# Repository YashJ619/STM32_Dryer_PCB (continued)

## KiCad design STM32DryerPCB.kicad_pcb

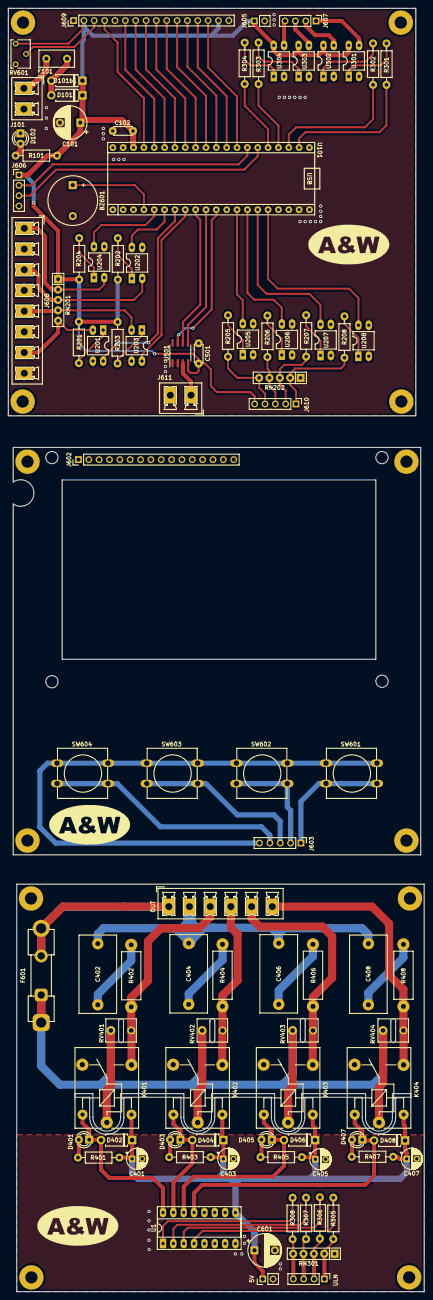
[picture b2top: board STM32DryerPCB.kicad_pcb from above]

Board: 2 copper layers, 102.1 x 315.0 mm, 111 parts (0 on the bottom side), 82 nets.

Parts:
BZ601: Buzzer; Buzzer_12x9.5RM7.6
C101: 220uF16v; CP_Radial_D8.0mm_P5.00mm
C102: 100nF; C_Disc_D4.3mm_W1.9mm_P5.00mm
C401, C403, C405, C407: 22uF; CP_Radial_D5.0mm_P2.50mm
C402, C404, C406, C408: 0.1uF; C_Rect_L19.0mm_W9.0mm_P15.00mm_MKS4
C501: 100n; C_Disc_D4.3mm_W1.9mm_P5.00mm
C601: 220uF16V; CP_Radial_D8.0mm_P5.00mm
D101, D101b1: 1N5819; D_A-405_P7.62mm_Horizontal
D102, D401, D403, D405, D407: LED; LED_D3.0mm
D402, D404, D406, D408: 1N4148; D_A-405_P7.62mm_Horizontal
F101: 1A; Fuse_Littelfuse_395Series
F601: 5A; Fuseholder_Clip-5x20mm_Keystone_3518P_Inline_P23.11x6.76mm_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
H601, H601#2, H601#4, H601#5: MountingHole; MountingHole_3mm
H601#3, H602, H603, H604, H605, H606, H607, H608, H609, H610, H611, H612: MountingHole; MountingHole_3mm_Pad
J101: DC_Con; PhoenixContact_MCV_1,5_2-G-5.08_1x02_P5.08mm_Vertical
J602: B1_B2_LCD; PinHeader_1x16_P2.54mm_Vertical
J603: B1_B2_KEYPAD; PinHeader_1x05_P2.54mm_Vertical
J605: B2_B3_PW; PinHeader_1x02_P2.54mm_Vertical
J606: B2_UART; PinHeader_1x04_P2.54mm_Vertical
J607: B2_B3_ULN; PinHeader_1x04_P2.54mm_Vertical
J608: B2_INPUT; PhoenixContact_MCV_1,5_8-G-5.08_1x08_P5.08mm_Vertical
J609: B2_B1_LCD; PinHeader_1x16_P2.54mm_Vertical
J610: B2_B1_KEYPAD; PinHeader_1x05_P2.54mm_Vertical
J611: B2_TEMP; PhoenixContact_MCV_1,5_2-G-5.08_1x02_P5.08mm_Vertical
J612: B3_B2_PW; PinHeader_1x02_P2.54mm_Vertical
J613: B3_output; PhoenixContact_MCV_1,5_6-G-5.08_1x06_P5.08mm_Vertical
J614: B3_B2_ULN; PinHeader_1x04_P2.54mm_Vertical
K401, K402, K403, K404: DC_5V; Relay_SPDT_SANYOU_SRD_Series_Form_C
R101: 1k; R_Axial_DIN0207_L6.3mm_D2.5mm_P10.16mm_Horizontal
R201, R202, R203, R204, R205, R206, R207, R208, R301, R302, R303, R304: 470R; R_Axial_DIN0207_L6.3mm_D2.5mm_P10.16mm_Horizontal
R305, R306, R307, R308, R401, R403, R405, R407: 1K; R_Axial_DIN0207_L6.3mm_D2.5mm_P10.16mm_Horizontal
R402, R404, R406, R408: 100R; R_Axial_DIN0414_L11.9mm_D4.5mm_P15.24mm_Horizontal
RN201, RN202, RN301: 10K; R_Array_SIP5
RV401, RV402, RV403, RV404: 10D431K; RV_Disc_D7mm_W5.7mm_P5mm
RV601: 10K; Potentiometer_Bourns_3266W_Vertical
SW601, SW602, SW603, SW604: SW_Push; SW_PUSH-12mm
U1: ULN2003A; DIP-16_W7.62mm_Socket_LongPads
U101: BluePill
U201, U202, U203, U204, U205, U206, U207, U208, U301, U302, U303, U304: PC817; DIP-4_W7.62mm_LongPads
U501: MAX6675; SOIC-8_3.9x4.9mm_P1.27mm

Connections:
#DRUM_LEFT: D407.1 (K), D408.2 (A), K404.5, U1.13 (O4)
#DRUM_RIGHT: D405.1 (K), D406.2 (A), K403.5, U1.14 (O3)
#FAN: D401.1 (K), D402.2 (A), K401.5, U1.16 (O1)
#HEATER: D403.1 (K), D404.2 (A), K402.5, U1.15 (O2)
+5V: C101.1, C102.1, C401.1, C403.1, C405.1, C407.1, C501.2, C601.1, D101.1 (K), D101b1.1 (K), D402.1 (K), D404.1 (K), D406.1 (K), D408.1 (K), J602.2, J602.15, J603.5, J605.1, J606.1, J609.2, J609.15, J610.5, J612.1, K401.2, K402.2, K403.2, K404.2, R101.2, R201.1, R202.1, R203.1, R204.1, R401.1, R403.1, R405.1, R407.1, RN201.1 (common), RV601.1, SW601.1, SW602.1, SW603.1, SW604.1, U1.9 (COM), U101.38 (5V), U301.4, U302.4, U303.4, U304.4, U501.4 (VCC)
/CONNECTORS/VO: J602.3, J609.3, RV601.2
/ULN2003/->FAN: R308.2, U1.1 (I1)
/ULN2003/->HEATER: R307.2, U1.2 (I2)
/ULN2003/->LEFT: R305.2, U1.4 (I4)
/ULN2003/->RIGHT: R306.2, U1.3 (I3)
BUZZER: BZ601.1 (-), U101.4 (PC15)
CS1: U101.9 (PA4), U501.6 (~CS)
DLEFT_ULNIN: J607.1, J614.1, R305.1, RN301.2 (R1), U301.3
DOOR_SW: U101.5 (PA0), U204.4
DOOR_SW_IN: J608.1, RN201.2 (R1), U204.2
DRIGHT_ULNIN: J607.2, J614.2, R306.1, RN301.3 (R2), U302.3
DRUM_LEFT: R301.1, U101.22 (PB13)
DRUM_LEFT_LINE: J613.6, K404.3, R408.1, RV404.2
DRUM_RIGHT: R302.1, U101.23 (PB14)
DRUM_RIGHT_LINE: J613.5, K403.3, R406.1, RV403.2
FAN: R304.1, U101.25 (PA8)
FAN_LINE: J613.3, K401.3, R402.1, RV401.2
FAN_ULNIN: J607.4, J614.4, R308.1, RN301.5 (R4), U304.3
FN_KEY_SW: U101.13 (PB0), U205.4
FN_KEY_SW_IN: J603.4, J610.4, R205.1, RN202.5 (R4), SW604.2
GND: BZ601.2 (+), C101.2, C102.2, C401.2, C403.2, C405.2, C407.2, C501.1, C601.2, D102.1 (K), J101.2, J602.1, J602.5, J602.16, J605.2, J606.4, J608.2, J608.4, J608.6, J608.8, J609.1, J609.5, J609.16, J611.2, J612.2, RN202.1 (common), RN301.1 (common), RV601.3, U1.8 (GND), U101.19 (GND), U101.20 (GND), U101.39 (GND), U201.3, U202.3, U203.3, U204.3, U205.2, U205.3, U206.2, U206.3, U207.2, U207.3, U208.2, U208.3, U301.2, U302.2, U303.2, U304.2, U501.1 (GND), U501.2 (T-)
HEATER: R303.1, U101.24 (PB15)
HEATER_LINE: J613.4, K402.3, R404.1, RV402.2
HEATER_SW: U101.8 (PA3), U203.4
HEATER_SW_IN: J608.5, RN201.4 (R3), U203.2
HEATER_ULNIN: J607.3, J614.3, R307.1, RN301.4 (R3), U303.3
HIGH_KEY_SW: U101.15 (PB10), U207.4
HIGH_KEY_SW_IN: J603.2, J610.2, R207.1, RN202.3 (R2), SW602.2
LCD_D0: J602.7, J609.7, U101.35 (PB7)
LCD_D1: J602.8, J609.8, U101.34 (PB6)
LCD_D2: J602.9, J609.9, U101.33 (PB5)
LCD_D3: J602.10, J609.10, U101.32 (PB4)
LCD_D4: J602.11, J609.11, U101.31 (PB3)
LCD_D5: J602.12, J609.12, U101.30 (PA15)
LCD_D6: J602.13, J609.13, U101.29 (PA12)
LCD_D7: J602.14, J609.14, U101.28 (PA11)
LCD_EN: J602.6, J609.6, U101.36 (PB8)
LCD_RS: J602.4, J609.4, U101.37 (PB9)
LIMIT_SW: U101.6 (PA1), U202.4
LIMIT_SW_IN: J608.3, RN201.3 (R2), U202.2
LINE: F601.1, K401.1, K402.1, K403.1, K404.1, RV401.1, RV402.1, RV403.1, RV404.1
LOW_KEY_SW: U101.14 (PB1), U206.4
LOW_KEY_SW_IN: J603.3, J610.3, R206.1, RN202.4 (R3), SW603.2
MID_KEY_SW: U101.16 (PB11), U208.4
MID_KEY_SW_IN: J603.1, J610.1, R208.1, RN202.2 (R1), SW601.2
MISO1: U101.11 (PA6), U501.7 (SO)
unnamed: C402.1, R402.2
unnamed: C404.1, R404.2
unnamed: C406.1, R406.2
unnamed: C408.1, R408.2
unnamed: D101.2 (A), D101b1.2 (A), F101.2
unnamed: D102.2 (A), R101.1
unnamed: D401.2 (A), R401.2
unnamed: D403.2 (A), R403.2
unnamed: D405.2 (A), R405.2
unnamed: D407.2 (A), R407.2
unnamed: F101.1, J101.1
unnamed: F601.2, J613.1
unnamed: R201.2, U201.1
unnamed: R202.2, U202.1
unnamed: R203.2, U203.1
unnamed: R204.2, U204.1
unnamed: R205.2, U205.1
unnamed: R206.2, U206.1
unnamed: R207.2, U207.1
unnamed: R208.2, U208.1
unnamed: R301.2, U301.1
unnamed: R302.2, U302.1
unnamed: R303.2, U303.1
unnamed: R304.2, U304.1
Neutral: C402.2, C404.2, C406.2, C408.2, J613.2
RX: J606.2, U101.27 (PA10)
SCK1: U101.10 (PA5), U501.5 (SCK)
SEL_ROT_SW: U101.7 (PA2), U201.4
SEL_ROT_SW_IN: J608.7, RN201.5 (R4), U201.2
TEMP+: J611.1, U501.3 (T+)
TX: J606.3, U101.26 (PA9)

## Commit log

2023-08-02 3 Story Dryer PCB
2023-08-02 Added 24v to 5v SMPS, Reduced it to 2 Story, Used Small Relays
2023-08-09 Fixed Boot pin not grounded
